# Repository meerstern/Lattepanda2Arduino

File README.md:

# Lattepanda2Arduino
The conversion adapter for Lattepanda.

[Lattepanda][1]のLeonardポートをArduino Lenardピッチへ変換するKicadファイルです。  

[1]: http://www.lattepanda.com/ "*1"

License - MIT

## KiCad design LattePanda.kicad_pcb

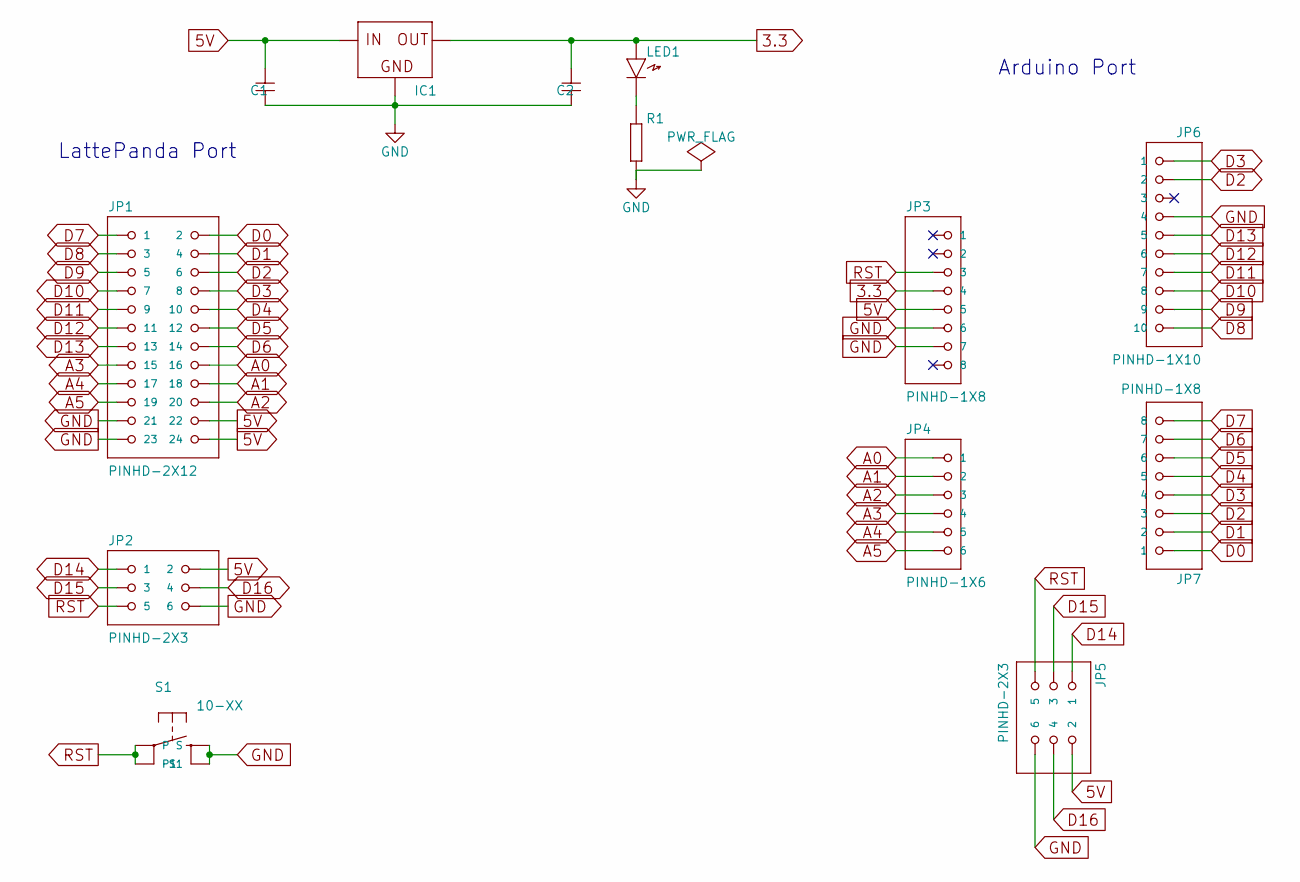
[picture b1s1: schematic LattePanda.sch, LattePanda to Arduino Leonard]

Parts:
C1, C2: CAPACITOR2012; generic-SMD2012
IC1: NJM2845MABDT; v-reg-DPACK
JP1: PINHD-2X12; pinhead-2X12
JP2, JP5: PINHD-2X3; pinhead-2X03
JP3, JP7: PINHD-1X8; pinhead-1X08
JP4: PINHD-1X6; pinhead-1X06
JP6: PINHD-1X10; pinhead-1X10
LED1: LED1608; generic-LED1608
R1: RESISTOR1608; generic-SMD1608
S1: 10-XX; switch-omron-B3F-10XX

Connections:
3.3: C2.1, IC1.3 (OUT), JP3.4, LED1.A
5V: C1.1, IC1.1 (IN), JP1.22, JP1.24, JP2.2, JP3.5, JP5.2
A0: JP1.16, JP4.1
A1: JP1.18, JP4.2
A2: JP1.20, JP4.3
A3: JP1.15, JP4.4
A4: JP1.17, JP4.5
A5: JP1.19, JP4.6
D0: JP1.2, JP7.1
D1: JP1.4, JP7.2
D2: JP1.6, JP6.2, JP7.3
D3: JP1.8, JP6.1, JP7.4
D4: JP1.10, JP7.5
D5: JP1.12, JP7.6
D6: JP1.14, JP7.7
D7: JP1.1, JP7.8
D8: JP1.3, JP6.10
D9: JP1.5, JP6.9
D10: JP1.7, JP6.8
D11: JP1.9, JP6.7
D12: JP1.11, JP6.6
D13: JP1.13, JP6.5
D14: JP2.1, JP5.1
D15: JP2.3, JP5.3
D16: JP2.4, JP5.4
GND: C1.2, C2.2, IC1.4 (GND), JP1.21, JP1.23, JP2.6, JP3.6, JP3.7, JP5.6, JP6.4, R1.2, S1.1 (S), S1.2 (S1)
unnamed: LED1.K, R1.1
RST: JP2.5, JP3.3, JP5.5, S1.3, S1.4 (P1)

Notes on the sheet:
LattePanda Port
Arduino Port

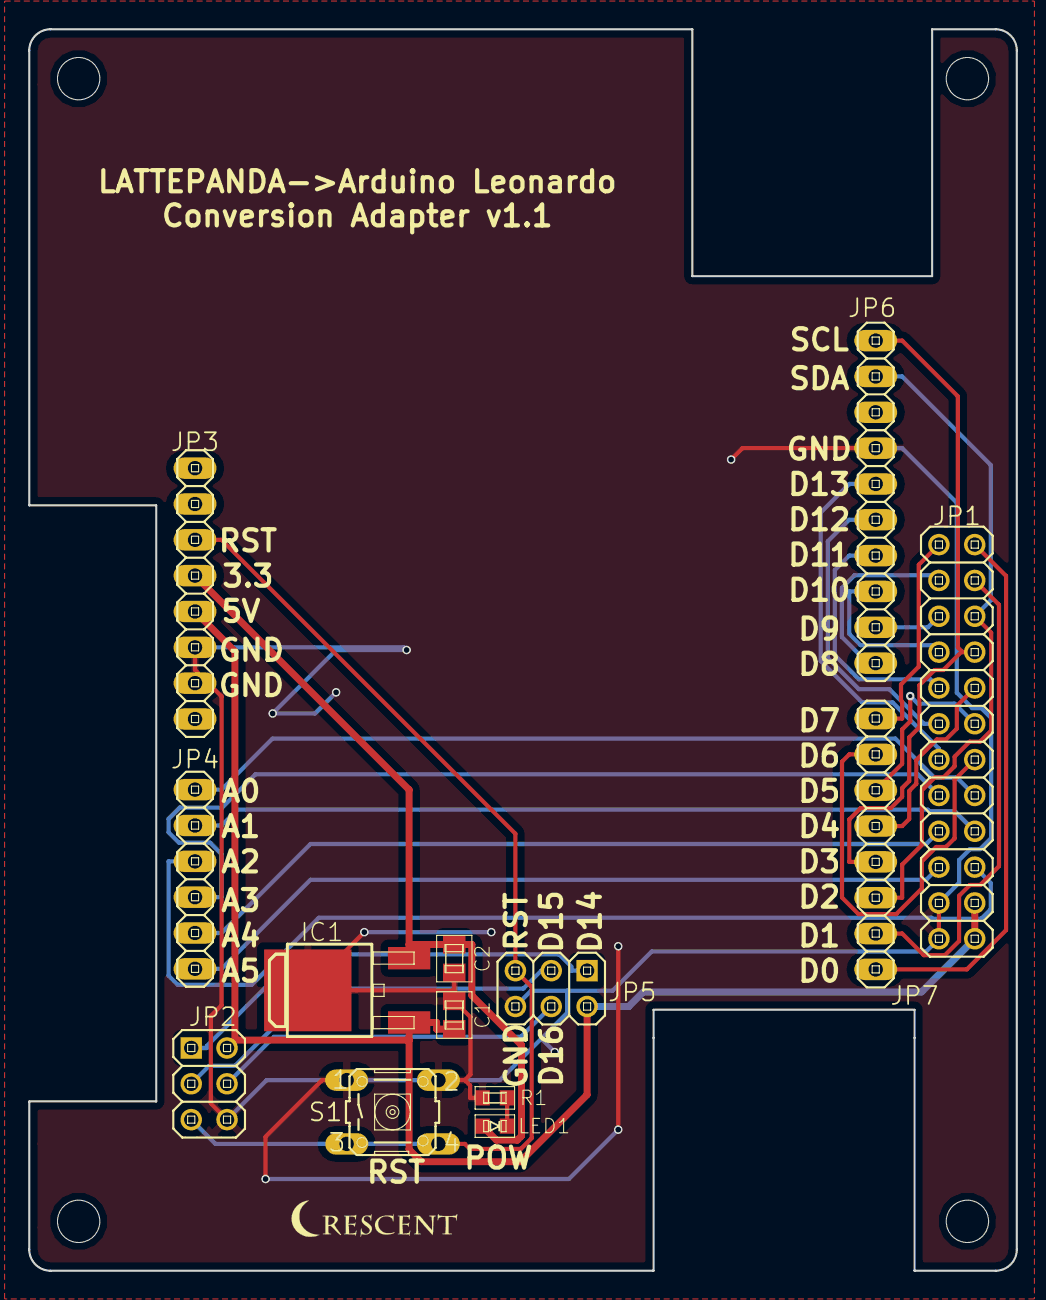
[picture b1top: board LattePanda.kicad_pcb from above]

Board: 2 copper layers, 70.0 x 88.0 mm, 17 parts (0 on the bottom side), 28 nets.

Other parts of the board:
REF1, REF2, REF3, REF4: MountingHole_3mm

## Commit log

2017-06-18 Init
2017-07-09 Fixed the interference of LAN port.
